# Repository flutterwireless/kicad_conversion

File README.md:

Flutter Basic KiCAD Version
==

I am working on converting Flutter (and myself) over to KiCAD.

This version is not yet ready to fab, but the copper is close and I am confident that moving to KiCAD will work.

Taylor

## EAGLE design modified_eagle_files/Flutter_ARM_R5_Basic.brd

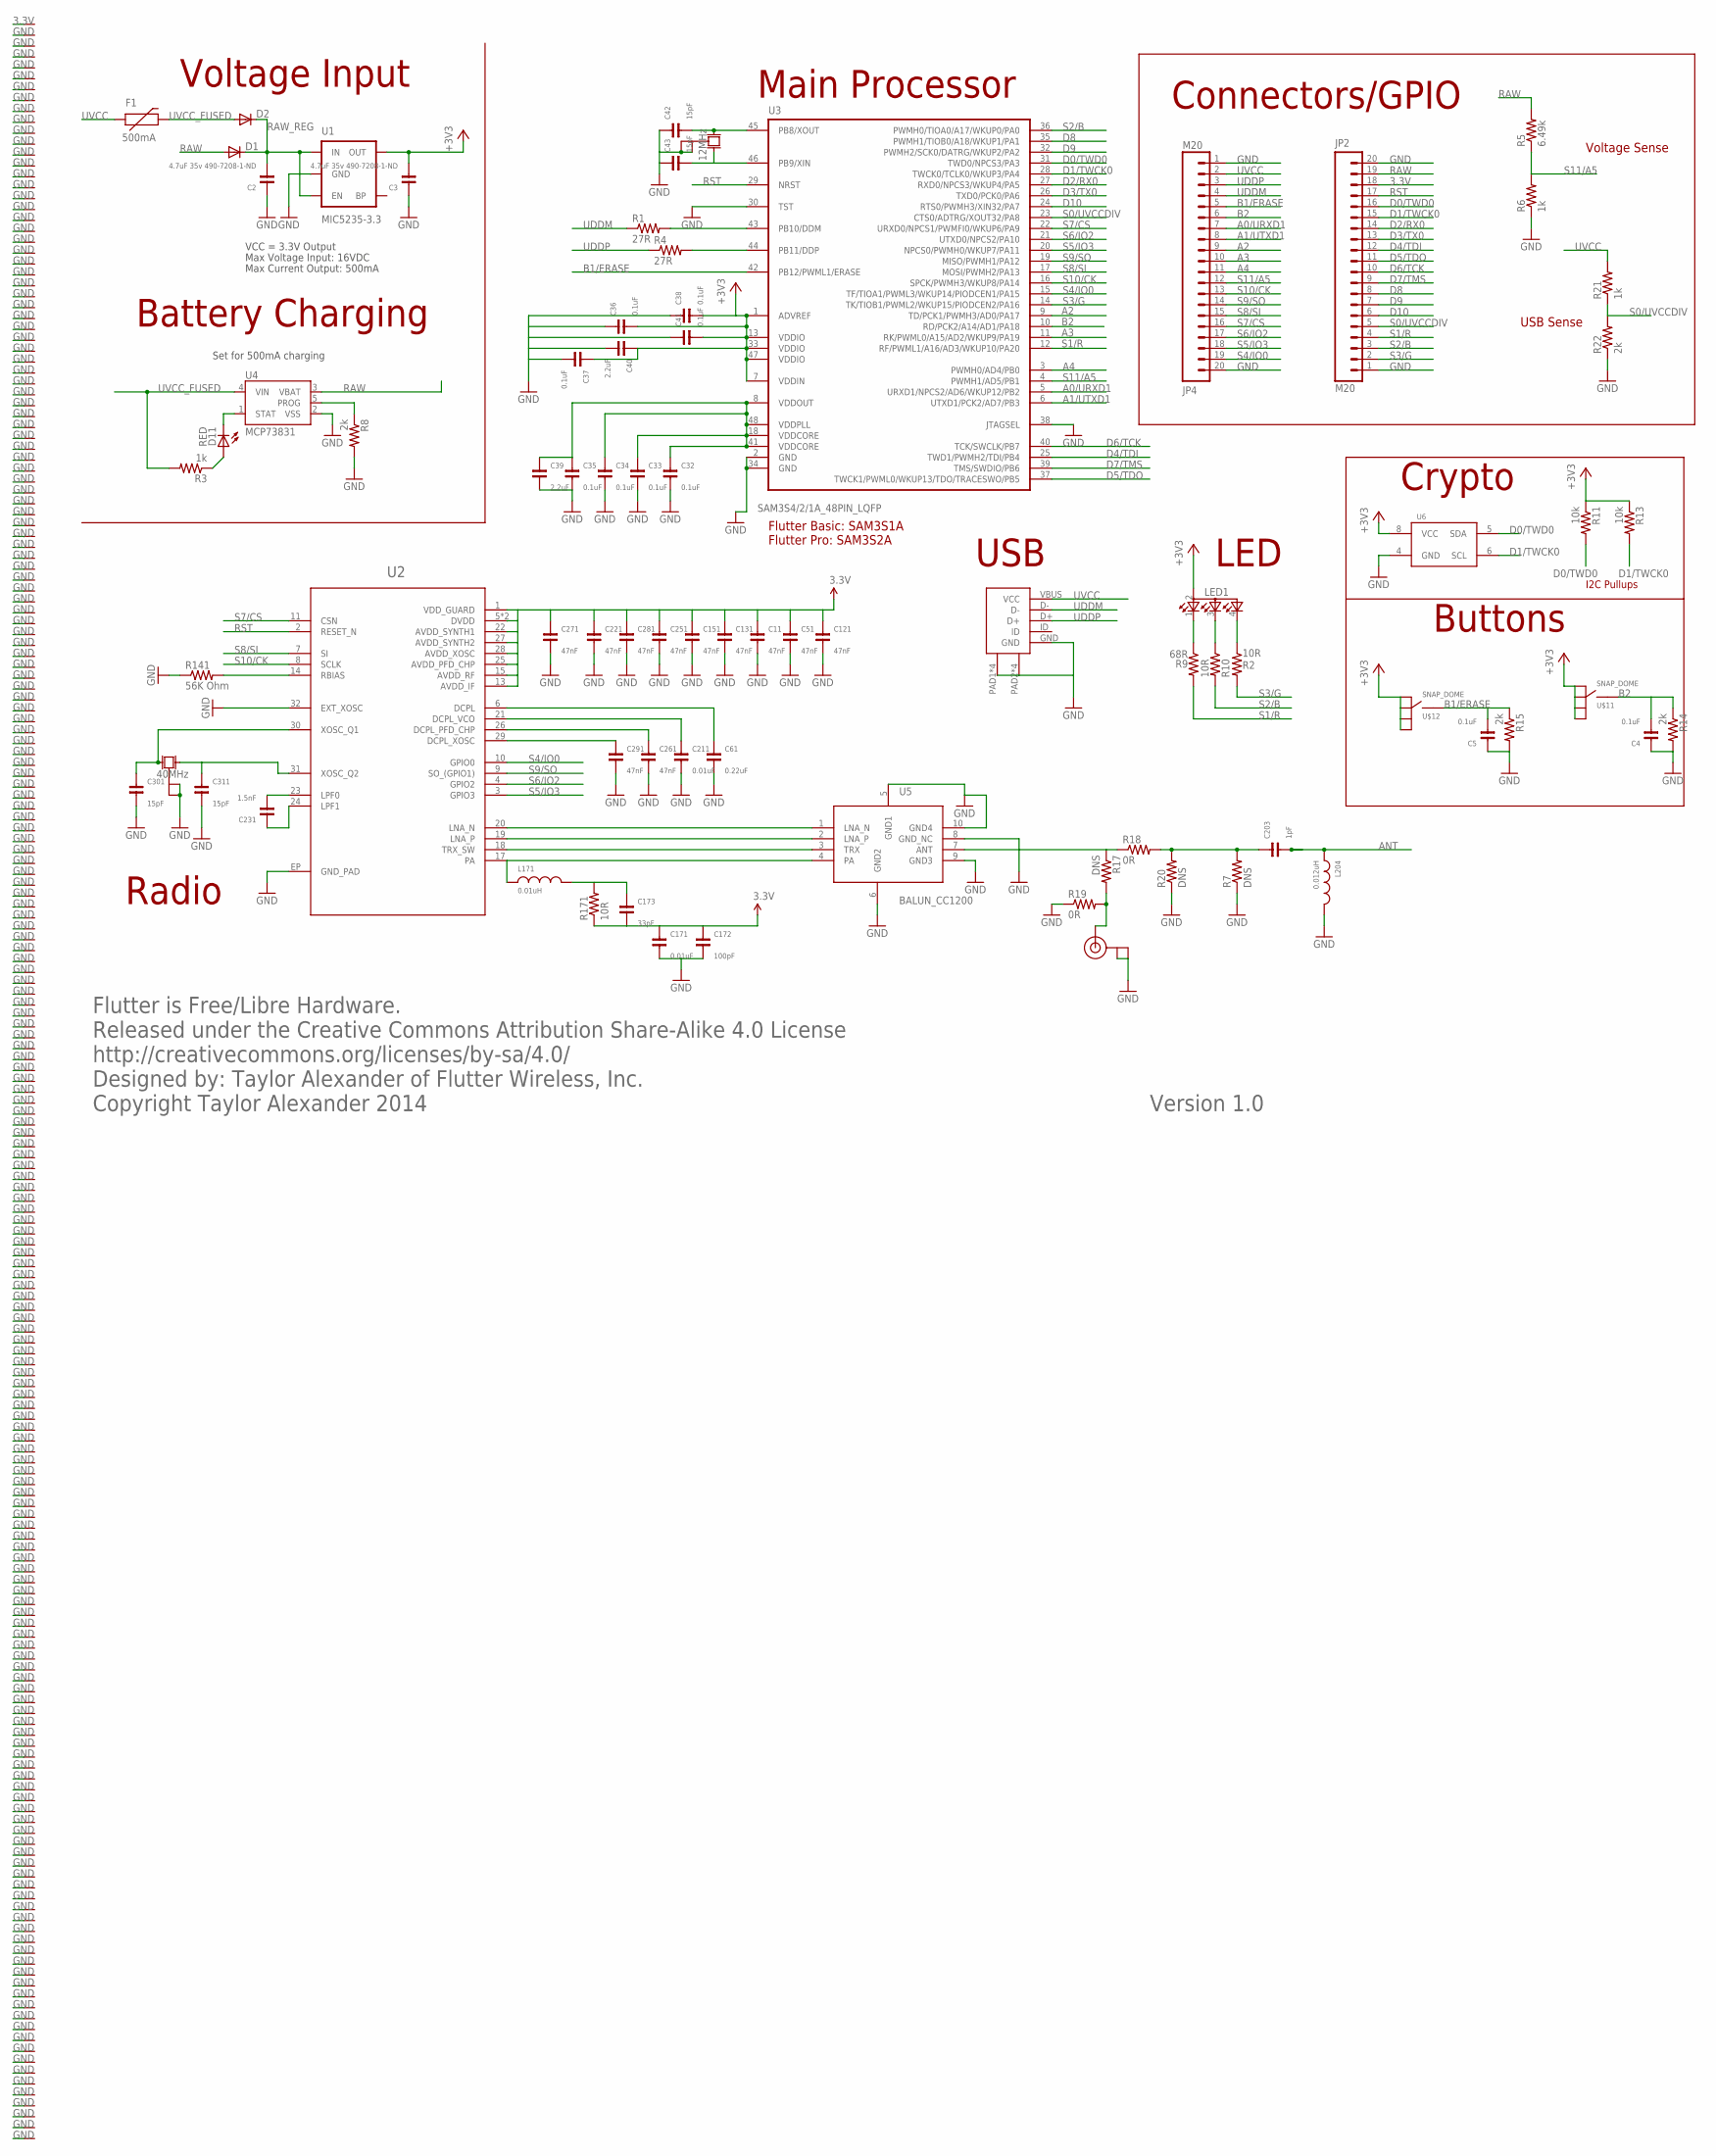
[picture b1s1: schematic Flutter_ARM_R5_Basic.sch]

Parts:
C2, C3: 4.7uF 35v 490-7208-1-ND; 0808-CAP
C4, C5, C32, C33, C34, C35, C36, C37, C38, C41: 0.1uF; 0402-CAP
C11, C51, C121, C131, C151, C221, C251, C261, C271, C281, C291: 47nF; 0402-CAP
C39, C40: 2.2uF; 0402-CAP
C42, C43, C301, C311: 15pF; 0402-CAP
C61: 0.22uF; 0402-CAP
C171, C211: 0.01uF; 0402-CAP
C172: 100pF; 0402-CAP
C173: 33pF; 0402-CAP
C203: 1pF; 0402-CAP
C231: 1.5nF; 0402-CAP
D1, D2: DIODESOD; SOD-323
D11: RED; LED-0603
F1: 500mA; 0603-PTC
JP2, JP4: M20; 1X20
L171: 0.01uH; 0402-IND
L204: 0.012uH; 0402-IND
LED1: TOPLED-3; P-LCC-4-3
R1, R4: 27R; 0402-RES
R2, R10, R171: 10R; 0402-RES
R3, R6, R21: 1k; 0402-RES
R5: 6.49k; 0402-RES
R7, R17, R20: DNS; 0402-RES
R8, R14, R15, R22: 2k; 0402-RES
R9: 68R; 0402-RES
R11, R13: 10k; 0402-RES
R18, R19: 0R; 0402-RES
R141: 56K Ohm; 0402-RES
U1: MIC5235-3.3; SOT23-5
U2: CC1200; QFN-32
U3: SAM3S4/2/1A_48PIN_LQFP; LQFP48
U4: MCP73831; SOT23-5
U5: BALUN_CC1200; IPC_BALUN_CC1200
U6: ATSHA204/ATECC108UDFN; UDFN_8_ATSHA204
U7: U.FL
U$2: MICRO_USB; MICRO-USB-SLOT-2
U$11, U$12: SNAP_DOME; 12MM_SNAP_DOME_SMALLER
VP_0, VP_1, VP_2, VP_3, VP_4, VP_5, VP_6, VP_7, VP_8, VP_9, VP_10, VP_11, VP_12, VP_13, VP_14, VP_15, VP_16, VP_17, VP_18, VP_19, VP_20, VP_21, VP_22, VP_23, VP_24, VP_25, VP_26, VP_27, VP_28, VP_29, VP_30, VP_31, VP_32, VP_33, VP_34, VP_35, VP_36, VP_37, VP_38, VP_39, VP_40, VP_41, VP_42, VP_43, VP_44, VP_45, VP_46, VP_47, VP_48, VP_49, VP_50, VP_51, VP_52, VP_53, VP_54, VP_55, VP_56, VP_57, VP_58, VP_59, VP_60, VP_61, VP_62, VP_63, VP_64, VP_65, VP_66, VP_67, VP_68, VP_69, VP_70, VP_71, VP_72, VP_73, VP_74, VP_78, VP_79, VP_80, VP_81, VP_82, VP_83, VP_84, VP_85, VP_86, VP_87, VP_88, VP_89, VP_90, VP_91, VP_92, VP_93, VP_94, VP_95, VP_96, VP_97, VP_98, VP_99, VP_100, VP_101, VP_102, VP_103, VP_104, VP_105, VP_106, VP_107, VP_108, VP_109, VP_110, VP_111, VP_112, VP_113, VP_114, VP_115, VP_116, VP_117, VP_118, VP_119, VP_120, VP_121, VP_122, VP_123, VP_124, VP_125, VP_126, VP_127, VP_128, VP_129, VP_130, VP_131, VP_132, VP_133, VP_134, VP_135, VP_136, VP_137, VP_138, VP_139, VP_140, VP_141, VP_142, VP_143, VP_144, VP_145, VP_146, VP_147, VP_148, VP_149, VP_150, VP_151, VP_152, VP_153, VP_154, VP_155, VP_156, VP_157, VP_158, VP_159, VP_160, VP_161, VP_162, VP_163, VP_164, VP_165, VP_166, VP_167, VP_168, VP_169, VP_170, VP_171, VP_172, VP_173, VP_174, VP_175, VP_176, VP_177, VP_178, VP_179, VP_180, VP_181, VP_182, VP_183, VP_184, VP_185, VP_186, VP_187, VP_188, VP_189, VP_190, VP_191, VP_192, VP_193, VP_194: VPDEV0; VPAC0
VP_75, VP_76, VP_77: VPDEV1; VPAC1
X1: 12MHz; XTAL_ABRACON_ABM8G_3.2MMX2.5MM
X2: 40MHz; XTAL_EPSON_FA_128_2MMX1.6MM

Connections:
3.3V: C3.2, C11.1, C36.2, C37.1, C38.2, C40.1, C41.2, C51.1, C121.1, C131.1, C151.1, C171.1, C172.1, C173.2, C221.1, C251.1, C271.1, C281.1, JP2.18, LED1.2 (A2), R11.1, R13.1, R171.1, U1.5 (OUT), U2.1 (VDD_GUARD), U2.5 (DVDD), U2.12 (DVDD), U2.13 (AVDD_IF), U2.15 (AVDD_RF), U2.22 (AVDD_SYNTH1), U2.25 (AVDD_PFD_CHP), U2.27 (AVDD_SYNTH2), U2.28 (AVDD_XOSC), U3.1 (ADVREF), U3.7 (VDDIN), U3.13 (VDDIO), U3.33 (VDDIO), U3.47 (VDDIO), U6.8 (VCC), U$11.P$1, U$11.P$2, U$11.P$3, U$11.P$4, U$12.P$1, U$12.P$2, U$12.P$3, U$12.P$4, VP_0.VP
+1.8V: C32.1, C33.1, C34.1, C35.1, C39.1, U3.8 (VDDOUT), U3.18 (VDDCORE), U3.41 (VDDCORE), U3.48 (VDDPLL)
A0/URXD1: JP4.7, U3.5 (URXD1/NPCS2/AD6/WKUP12/PB2)
A1/UTXD1: JP4.8, U3.6 (UTXD1/PCK2/AD7/PB3)
A2: JP4.9, U3.9 (TD/PCK1/PWMH3/AD0/PA17)
A3: JP4.10, U3.11 (RK/PWML0/A15/AD2/WKUP9/PA19)
A4: JP4.11, U3.3 (PWMH0/AD4/PB0)
ANT: C203.2, L204.1
B1/ERASE: C5.2, JP4.5, R15.1, U3.42 (PB12/PWML1/ERASE), U$12.CENTER
B2: C4.2, JP4.6, R14.1, U3.10 (RD/PCK2/A14/AD1/PA18), U$11.CENTER
D0/TWD0: JP2.16, R11.2, U3.31 (TWD0/NPCS3/PA3), U6.5 (SDA)
D1/TWCK0: JP2.15, R13.2, U3.28 (TWCK0/TCLK0/WKUP3/PA4), U6.6 (SCL)
D2/RX0: JP2.14, U3.27 (RXD0/NPCS3/WKUP4/PA5)
D3/TX0: JP2.13, U3.26 (TXD0/PCK0/PA6)
D4/TDI: JP2.12, U3.25 (TWD1/PWMH2/TDI/PB4)
D5/TDO: JP2.11, U3.37 (TWCK1/PWML0/WKUP13/TDO/TRACESWO/PB5)
D6/TCK: JP2.10, U3.40 (TCK/SWCLK/PB7)
D7/TMS: JP2.9, U3.39 (TMS/SWDIO/PB6)
D8: JP2.8, U3.35 (PWMH1/TIOB0/A18/WKUP1/PA1)
D9: JP2.7, U3.32 (PWMH2/SCK0/DATRG/WKUP2/PA2)
D10: JP2.6, U3.24 (RTS0/PWMH3/XIN32/PA7)
GND: C2.1, C3.1, C4.1, C5.1, C11.2, C32.2, C33.2, C34.2, C35.2, C36.1, C37.2, C38.1, C39.2, C40.2, C41.1, C42.1, C43.1, C51.2, C61.2, C121.2, C131.2, C151.2, C171.2, C172.2, C211.2, C221.2, C251.2, C261.2, C271.2, C281.2, C291.2, C301.2, C311.2, JP2.1, JP2.20, JP4.1, JP4.20, L204.2, R6.1, R7.1, R8.2, R14.2, R15.2, R19.1, R20.1, R22.1, R141.1, U1.2 (GND), U2.32 (EXT_XOSC), U2.EP (GND_PAD), U3.2 (GND), U3.30 (TST), U3.34 (GND), U3.38 (JTAGSEL), U4.2 (VSS), U5.5 (GND1), U5.6 (GND2), U5.8 (GND_NC), U5.9 (GND3), U5.10 (GND4), U6.4 (GND), U7.P$1 (GND), U7.P$2 (GND), U$2.GND, U$2.PAD1, U$2.PAD2, U$2.PAD3, U$2.PAD4, U$2.PAD5, U$2.PAD6, U$2.PAD7, U$2.PAD8, VP_1.VP, VP_2.VP, VP_3.VP, VP_4.VP, VP_5.VP, VP_6.VP, VP_7.VP, VP_8.VP, VP_9.VP, VP_10.VP, VP_11.VP, VP_12.VP, VP_13.VP, VP_14.VP, VP_15.VP, VP_16.VP, VP_17.VP, VP_18.VP, VP_19.VP, VP_20.VP, VP_21.VP, VP_22.VP, VP_23.VP, VP_24.VP, VP_25.VP, VP_26.VP, VP_27.VP, VP_28.VP, VP_29.VP, VP_30.VP, VP_31.VP, VP_32.VP, VP_33.VP, VP_34.VP, VP_35.VP, VP_36.VP, VP_37.VP, VP_38.VP, VP_39.VP, VP_40.VP, VP_41.VP, VP_42.VP, VP_43.VP, VP_44.VP, VP_45.VP, VP_46.VP, VP_47.VP, VP_48.VP, VP_49.VP, VP_50.VP, VP_51.VP, VP_52.VP, VP_53.VP, VP_54.VP, VP_55.VP, VP_56.VP, VP_57.VP, VP_58.VP, VP_59.VP, VP_60.VP, VP_61.VP, VP_62.VP, VP_63.VP, VP_64.VP, VP_65.VP, VP_66.VP, VP_67.VP, VP_68.VP, VP_69.VP, VP_70.VP, VP_71.VP, VP_72.VP, VP_73.VP, VP_74.VP, VP_75.VP, VP_76.VP, VP_77.VP, VP_78.VP, VP_79.VP, VP_80.VP, VP_81.VP, VP_82.VP, VP_83.VP, VP_84.VP, VP_85.VP, VP_86.VP, VP_87.VP, VP_88.VP, VP_89.VP, VP_90.VP, VP_91.VP, VP_92.VP, VP_93.VP, VP_94.VP, VP_95.VP, VP_96.VP, VP_97.VP, VP_98.VP, VP_99.VP, VP_100.VP, VP_101.VP, VP_102.VP, VP_103.VP, VP_104.VP, VP_105.VP, VP_106.VP, VP_107.VP, VP_108.VP, VP_109.VP, VP_110.VP, VP_111.VP, VP_112.VP, VP_113.VP, VP_114.VP, VP_115.VP, VP_116.VP, VP_117.VP, VP_118.VP, VP_119.VP, VP_120.VP, VP_121.VP, VP_122.VP, VP_123.VP, VP_124.VP, VP_125.VP, VP_126.VP, VP_127.VP, VP_128.VP, VP_129.VP, VP_130.VP, VP_131.VP, VP_132.VP, VP_133.VP, VP_134.VP, VP_135.VP, VP_136.VP, VP_137.VP, VP_138.VP, VP_139.VP, VP_140.VP, VP_141.VP, VP_142.VP, VP_143.VP, VP_144.VP, VP_145.VP, VP_146.VP, VP_147.VP, VP_148.VP, VP_149.VP, VP_150.VP, VP_151.VP, VP_152.VP, VP_153.VP, VP_154.VP, VP_155.VP, VP_156.VP, VP_157.VP, VP_158.VP, VP_159.VP, VP_160.VP, VP_161.VP, VP_162.VP, VP_163.VP, VP_164.VP, VP_165.VP, VP_166.VP, VP_167.VP, VP_168.VP, VP_169.VP, VP_170.VP, VP_171.VP, VP_172.VP, VP_173.VP, VP_174.VP, VP_175.VP, VP_176.VP, VP_177.VP, VP_178.VP, VP_179.VP, VP_180.VP, VP_181.VP, VP_182.VP, VP_183.VP, VP_184.VP, VP_185.VP, VP_186.VP, VP_187.VP, VP_188.VP, VP_189.VP, VP_190.VP, VP_191.VP, VP_192.VP, VP_193.VP, VP_194.VP, X1.P$2 (GND), X1.P$4 (GND), X2.2 (GND), X2.4 (GND)
LNA_N: U2.20 (LNA_N), U5.1 (LNA_N)
LNA_P: U2.19 (LNA_P), U5.2 (LNA_P)
unnamed: C61.1, U2.6 (DCPL)
unnamed: R141.2, U2.14 (RBIAS)
unnamed: C231.1, U2.24 (LPF1)
unnamed: C231.2, U2.23 (LPF0)
unnamed: C211.1, U2.21 (DCPL_VCO)
unnamed: D11.A, R3.1
unnamed: C173.1, L171.2, R171.2
unnamed: C203.1, R7.2, R18.2, R20.2
unnamed: R17.1, R18.1, U5.7 (ANT)
unnamed: R17.2, R19.2, U7.P$3 (SIGNAL)
unnamed: C311.1, U2.31 (XOSC_Q2), X2.1 (X1)
unnamed: C261.1, U2.26 (DCPL_PFD_CHP)
unnamed: C301.1, U2.30 (XOSC_Q1), X2.3 (X2)
unnamed: C291.1, U2.29 (DCPL_XOSC)
unnamed: LED1.1 (CRED), R9.1
unnamed: LED1.4 (CGREEN), R2.1
unnamed: C42.2, U3.45 (PB8/XOUT), X1.P$3 (X2)
unnamed: C43.2, U3.46 (PB9/XIN), X1.P$1 (X1)
PA: L171.1, U2.17 (PA), U5.4 (PA)
PROG: R8.1, U4.5 (PROG)
RAW: D1.2 (A), JP2.19, R5.2, U4.3 (VBAT)
RAW_REG: C2.2, D1.1 (C), D2.1 (C), U1.1 (IN), U1.3 (EN)
RST: JP2.17, U2.2 (RESET_N), U3.29 (NRST)
S0/UVCCDIV: JP2.5, R21.1, R22.2, U3.23 (CTS0/ADTRG/XOUT32/PA8)
S1/R: JP2.4, R9.2, U3.12 (RF/PWML1/A16/AD3/WKUP10/PA20)
S2/B: JP2.3, R10.2, U3.36 (PWMH0/TIOA0/A17/WKUP0/PA0)
S3/G: JP2.2, R2.2, U3.14 (TK/TIOB1/PWML2/WKUP15/PIODCEN2/PA16)
S4/IO0: JP4.19, U2.10 (GPIO0), U3.15 (TF/TIOA1/PWML3/WKUP14/PIODCEN1/PA15)
S5/IO3: JP4.18, U2.3 (GPIO3), U3.20 (NPCS0/PWMH0/WKUP7/PA11)
S6/IO2: JP4.17, U2.4 (GPIO2), U3.21 (UTXD0/NPCS2/PA10)
S7/CS: JP4.16, U2.11 (CSN), U3.22 (URXD0/NPCS1/PWMFI0/WKUP6/PA9)
S8/SI: JP4.15, U2.7 (SI), U3.17 (MOSI/PWMH2/PA13)
S9/SO: JP4.14, U2.9 (SO_(GPIO1)), U3.19 (MISO/PWMH1/PA12)
S10/CK: JP4.13, U2.8 (SCLK), U3.16 (SPCK/PWMH3/WKUP8/PA14)
S11/A5: JP4.12, R5.1, R6.2, U3.4 (PWMH1/AD5/PB1)
STAT: D11.C, U4.1 (STAT)
TRX_SW: U2.18 (TRX_SW), U5.3 (TRX)
U7: LED1.3 (CBLUE), R10.1
UDDC_+: R4.2, U3.44 (PB11/DDP)
UDDC_-: R1.2, U3.43 (PB10/DDM)
UDDM: JP4.4, R1.1, U$2.D-
UDDP: JP4.3, R4.1, U$2.D+
UVCC: F1.1, JP4.2, R21.2, U$2.VBUS (VCC)
UVCC_FUSED: D2.2 (A), F1.2, R3.2, U4.4 (VIN)

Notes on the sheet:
Max Voltage Input: 16VDC
Max Current Output: 500mA
VCC = 3.3V Output
Flutter is Free/Libre Hardware. Released under the Creative Commons Attribution Share-Alike 4.0 License http://creativecommons.org/licenses/by-sa/4.0/ Designed by: Taylor Alexander of Flutter Wireless, Inc. Copyright Taylor Alexander 2014
I2C Pullups
Set for 500mA charging
Voltage Input
Battery Charging
Main Processor
Connectors/GPIO
Radio
Buttons
Crypto
USB
LED
Flutter Basic: SAM3S1A Flutter Pro: SAM3S2A
Voltage Sense
USB Sense
Version 1.0

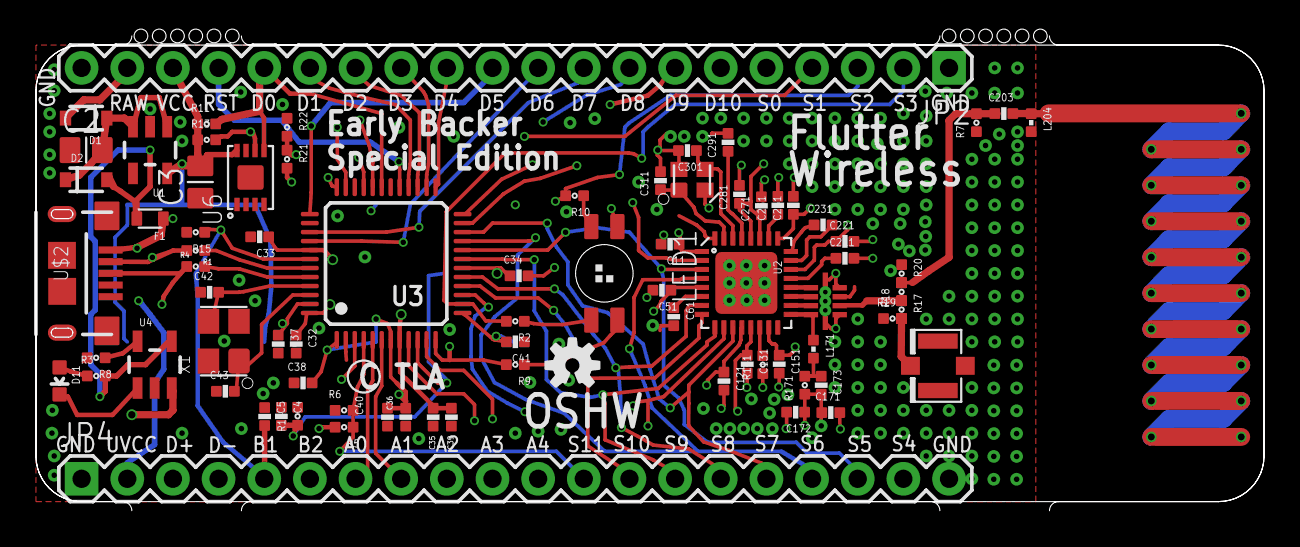
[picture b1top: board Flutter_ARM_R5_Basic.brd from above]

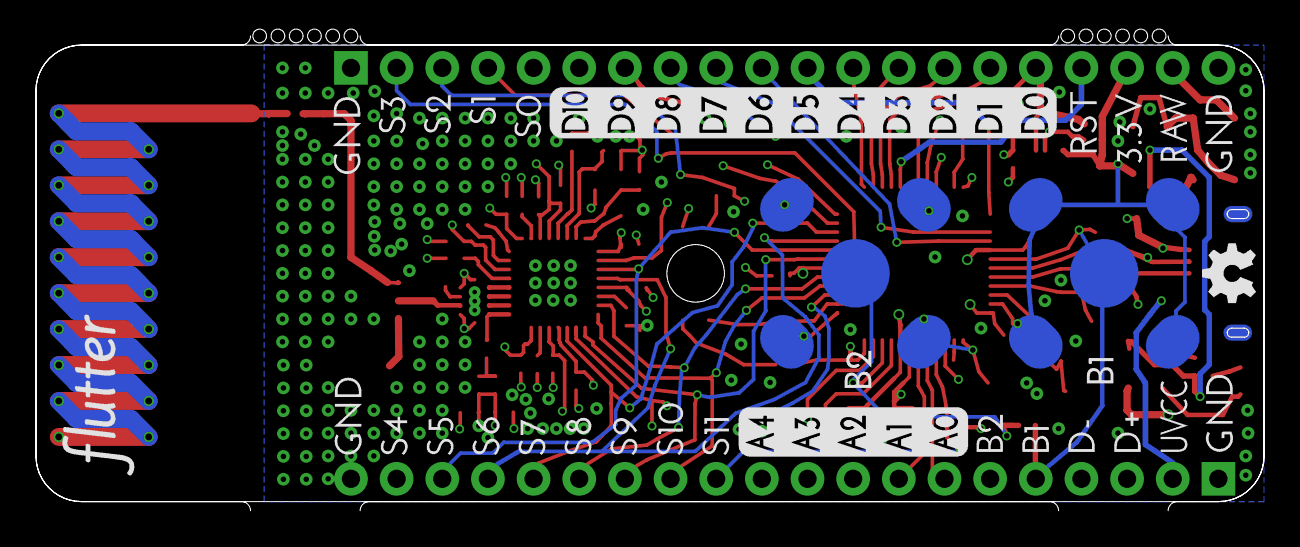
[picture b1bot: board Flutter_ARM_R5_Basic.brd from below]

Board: 4 copper layers, 68.3 x 26.4 mm, 275 parts (2 on the bottom side), 68 nets.

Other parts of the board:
U$1: OSHW-LOGOS; OSHW-LOGO-S

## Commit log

2018-01-29 Initial Commit. Converting Flutter Basic to KiCAD.
2018-01-29 Add Readme

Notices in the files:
parts and their libraries:
SparkFun-Aesthetics: Licensing: CC v3.0 Share-Alike You are welcome to use this library for commercial purposes.
